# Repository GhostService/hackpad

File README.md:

# Ghost's Hackpad #
*Made for HC's Stardance*

This is the KiCad project for my hackpad project. I will be updating this as I go with other files, such as the firmware and photos of the complete product.

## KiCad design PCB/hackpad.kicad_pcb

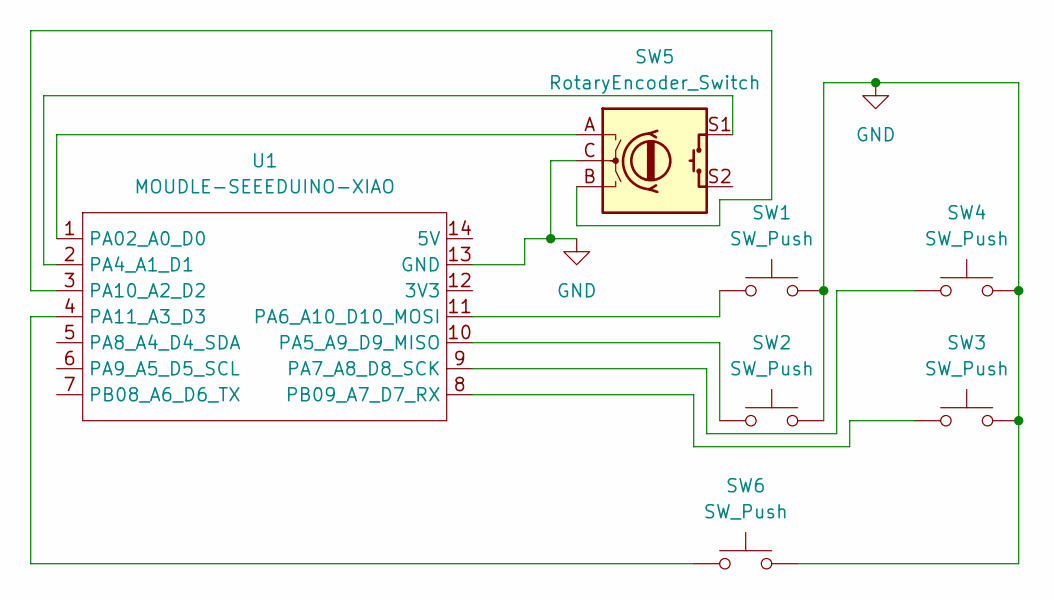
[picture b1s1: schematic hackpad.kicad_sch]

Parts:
SW1, SW2, SW3, SW4, SW6: SW_Push; SW_Cherry_MX_1.00u_PCB
SW5: RotaryEncoder_Switch; RotaryEncoder_Alps_EC11E-Switch_Vertical_H20mm
U1: MOUDLE-SEEEDUINO-XIAO; XIAO-Generic-Hybrid-14P-2.54-21X17.8MM

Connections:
GND: SW1.2, SW2.2, SW3.2, SW4.2, SW5.C, SW6.2, U1.13 (GND)
unnamed: SW5.A, U1.1 (PA02_A0_D0)
unnamed: SW5.S1, U1.2 (PA4_A1_D1)
unnamed: SW2.1, U1.10 (PA5_A9_D9_MISO)
unnamed: SW1.1, U1.11 (PA6_A10_D10_MOSI)
unnamed: SW4.1, U1.9 (PA7_A8_D8_SCK)
unnamed: SW5.B, U1.3 (PA10_A2_D2)
unnamed: SW6.1, U1.4 (PA11_A3_D3)
unnamed: SW3.1, U1.8 (PB09_A7_D7_RX)

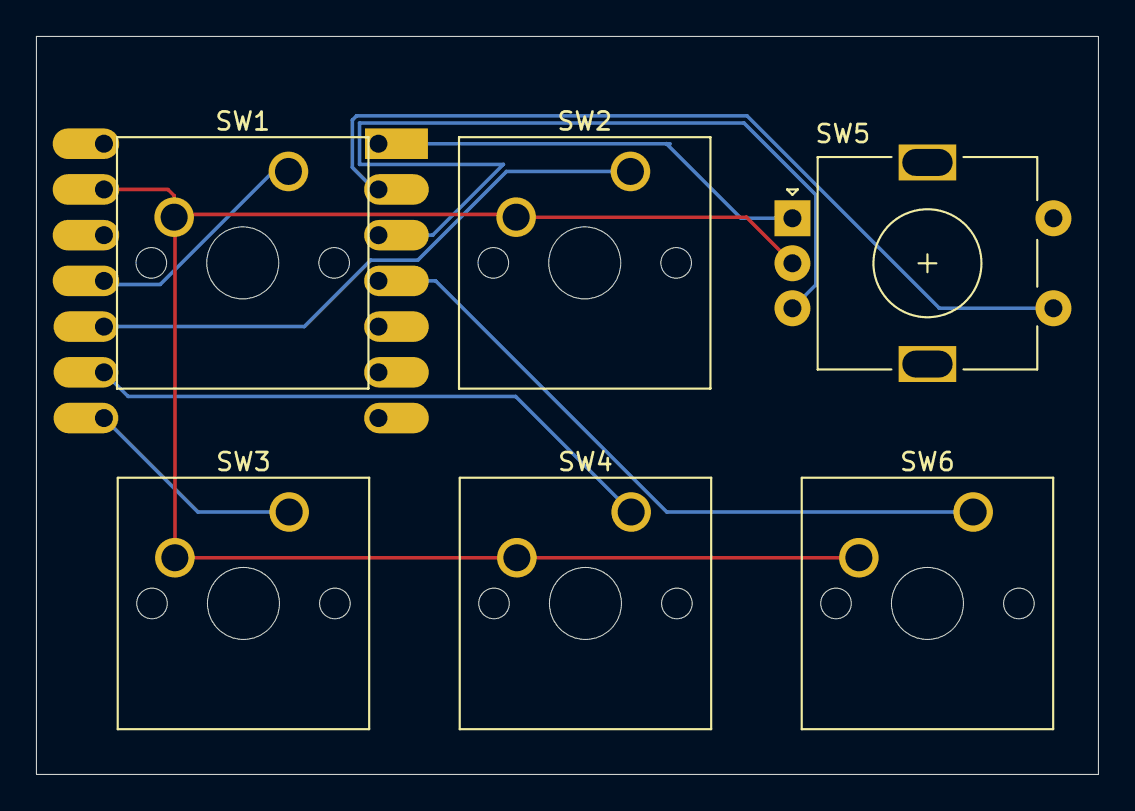
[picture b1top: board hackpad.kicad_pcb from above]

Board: 2 copper layers, 59.0 x 41.0 mm, 7 parts (1 on the bottom side), 9 nets.

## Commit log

2026-06-03 init
2026-06-03 update shi
